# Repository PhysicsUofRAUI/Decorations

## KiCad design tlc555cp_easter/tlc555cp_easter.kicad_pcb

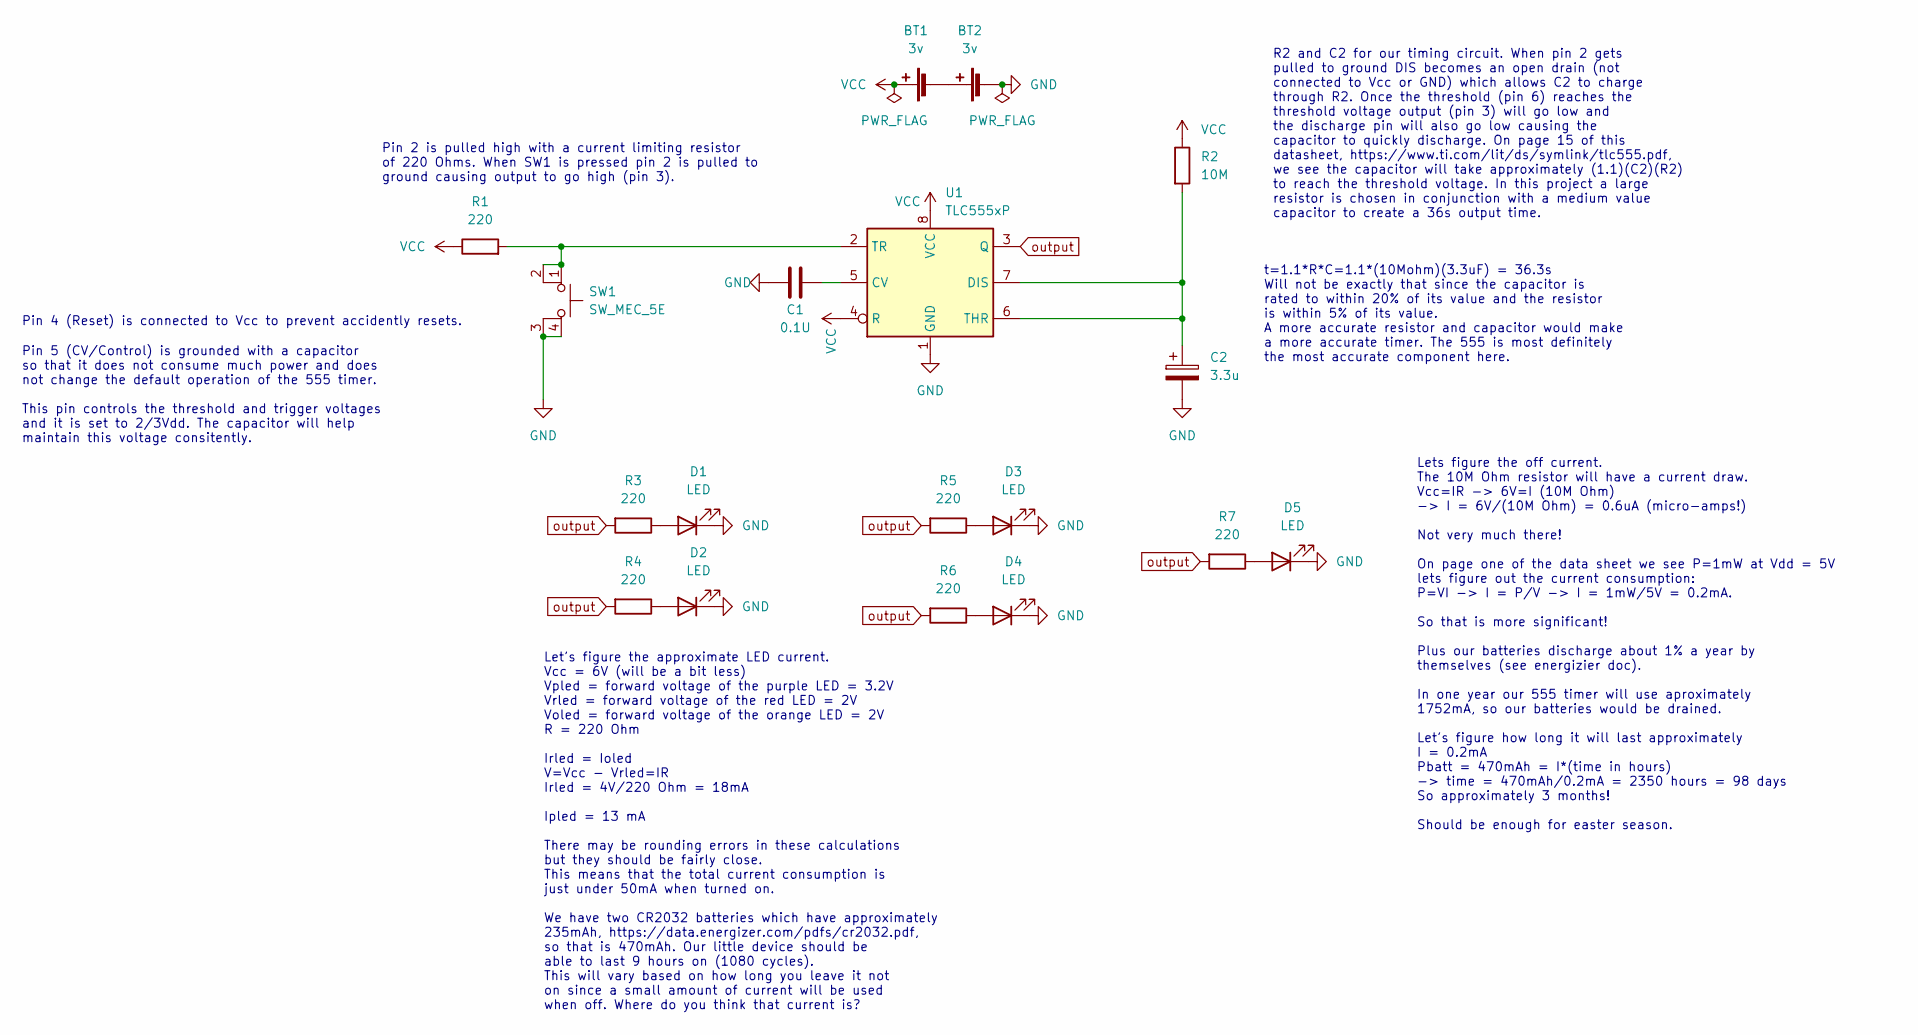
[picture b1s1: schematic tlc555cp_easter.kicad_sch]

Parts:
BT1, BT2: 3v; 1066
C1: 0.1U; CP_Radial_D5.0mm_P2.50mm
C2: 3.3u; CP_Radial_D5.0mm_P2.50mm
D1, D2, D3, D4, D5: LED; LED_D5.0mm
R1, R3, R4, R5, R6, R7: 220; R_Axial_DIN0204_L3.6mm_D1.6mm_P7.62mm_Horizontal
R2: 10M; R_Axial_DIN0204_L3.6mm_D1.6mm_P7.62mm_Horizontal
SW1: SW_MEC_5E; SW_PUSH-12mm_kody
U1: TLC555xP; DIP-8_W7.62mm

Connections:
GND: BT2.2 (-), C1.2, C2.2, D1.1 (K), D2.1 (K), D3.1 (K), D4.1 (K), D5.1 (K), SW1.3 (K), SW1.4 (A), U1.1 (GND)
unnamed: BT1.2 (-), BT2.1 (+)
unnamed: C2.1, R2.2, U1.6 (THR), U1.7 (DIS)
unnamed: D1.2 (A), R3.1
unnamed: D2.2 (A), R4.1
unnamed: D3.2 (A), R5.1
unnamed: D4.2 (A), R6.1
unnamed: D5.2 (A), R7.1
unnamed: R1.2, SW1.1, SW1.2, U1.2 (TR)
unnamed: C1.1, U1.5 (CV)
VCC: BT1.1 (+), R1.1, R2.1, U1.4 (R), U1.8 (VCC)
output: R3.2, R4.2, R5.2, R6.2, R7.2, U1.3 (Q)

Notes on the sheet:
Pin 4 (Reset) is connected to Vcc to prevent accidently resets.
t=1.1*R*C=1.1*(10Mohm)(3.3uF) = 36.3s Will not be exactly that since the capacitor is rated to within 20% of its value and the resistor is within 5% of its value. A more accurate resistor and capacitor would make a more accurate timer. The 555 is most definitely the most accurate component here.
Pin 2 is pulled high with a current limiting resistor of 220 Ohms. When SW1 is pressed pin 2 is pulled to ground causing output to go high (pin 3).
Pin 5 (CV/Control) is grounded with a capacitor so that it does not consume much power and does not change the default operation of the 555 timer. This pin controls the threshold and trigger voltages and it is set to 2/3Vdd. The capacitor will help maintain this voltage consitently.
Lets figure the off current. The 10M Ohm resistor will have a current draw. Vcc=IR -> 6V=I (10M Ohm) -> I = 6V/(10M Ohm) = 0.6uA (micro-amps!) Not very much there! On page one of the data sheet we see P=1mW at Vdd = 5V lets figure out the current consumption: P=VI -> I = P/V -> I = 1mW/5V = 0.2mA. 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
Let's figure the approximate LED current. Vcc = 6V (will be a bit less) Vpled = forward voltage of the purple LED = 3.2V Vrled = forward voltage of the red LED = 2V Voled = forward voltage of the orange LED = 2V R = 220 Ohm Irled = Ioled V=Vcc - Vrled=IR Irled = 4V/220 Ohm = 18mA Ipled = 13 mA Ther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
R2 and C2 for our timing circuit. When pin 2 gets pulled to ground DIS becomes an open drain (not connected to Vcc or GND) which allows C2 to charge through R2. Once the threshold (pin 6) reaches the threshold voltage output (pin 3) will go low and the discharge pin will also go low causing the cap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

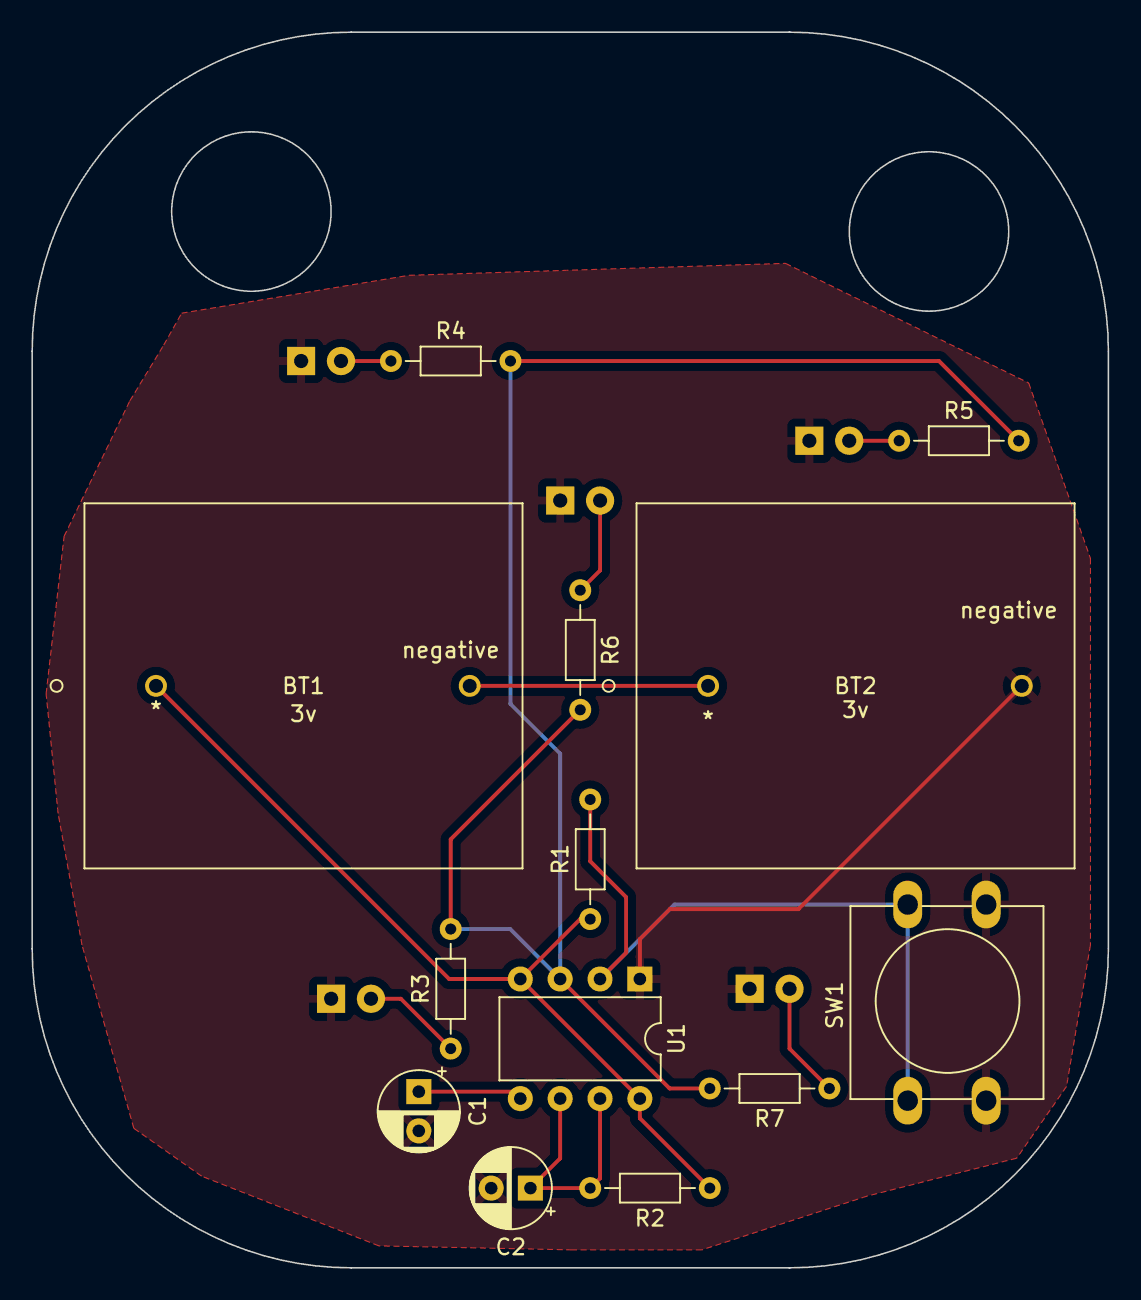
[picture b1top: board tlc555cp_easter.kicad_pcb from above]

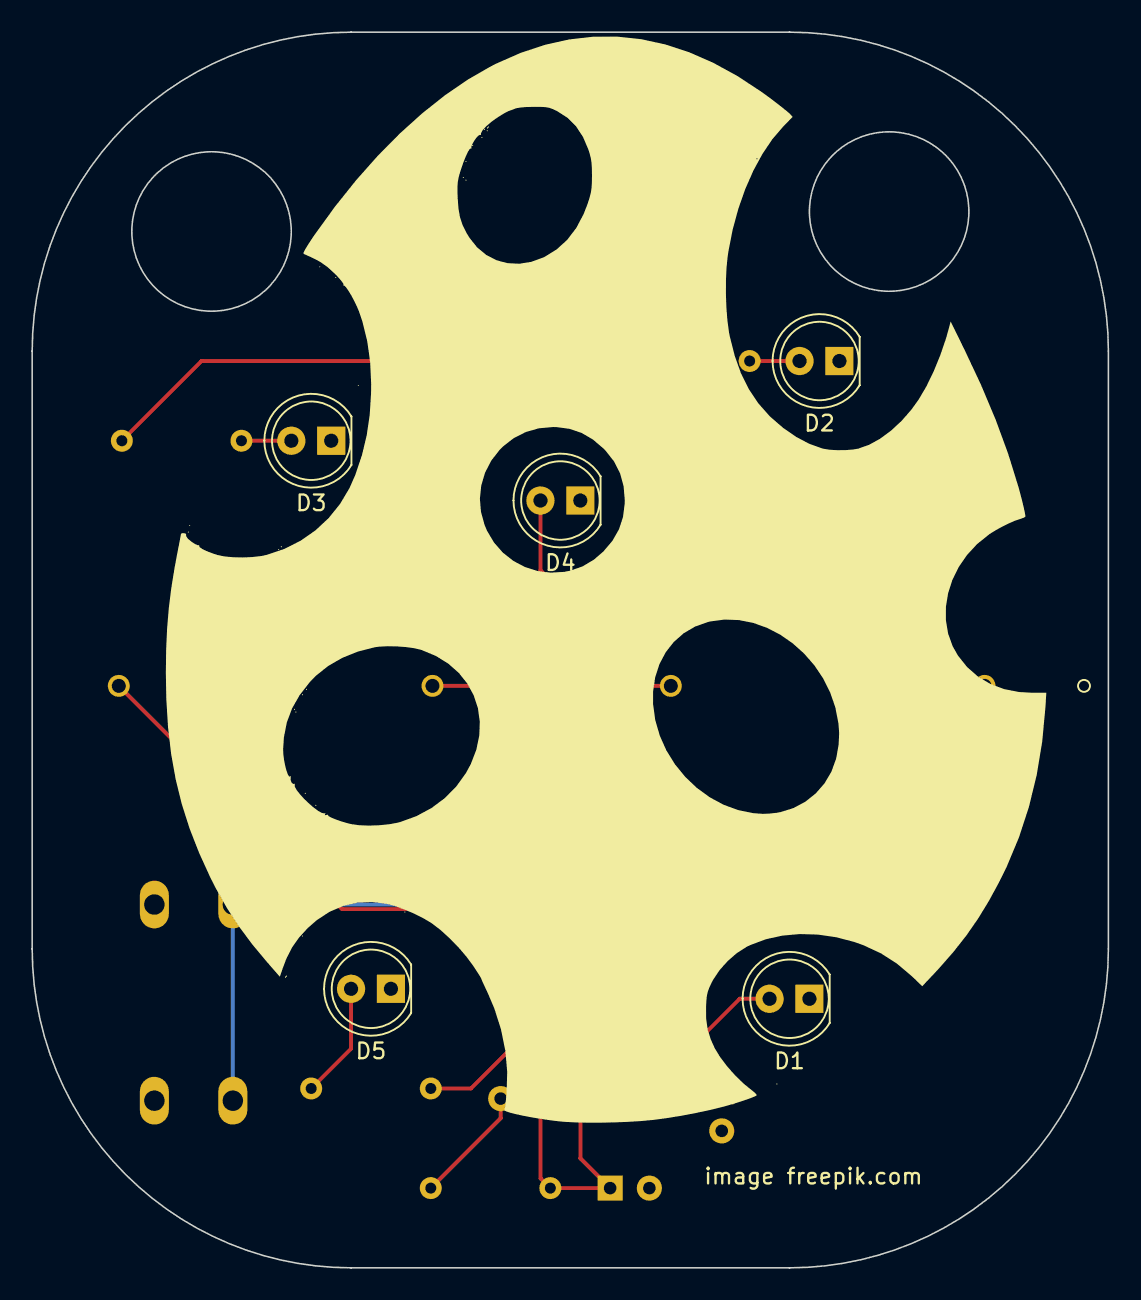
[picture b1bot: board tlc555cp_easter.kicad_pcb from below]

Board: 2 copper layers, 68.6 x 78.7 mm, 18 parts (5 on the bottom side), 12 nets.

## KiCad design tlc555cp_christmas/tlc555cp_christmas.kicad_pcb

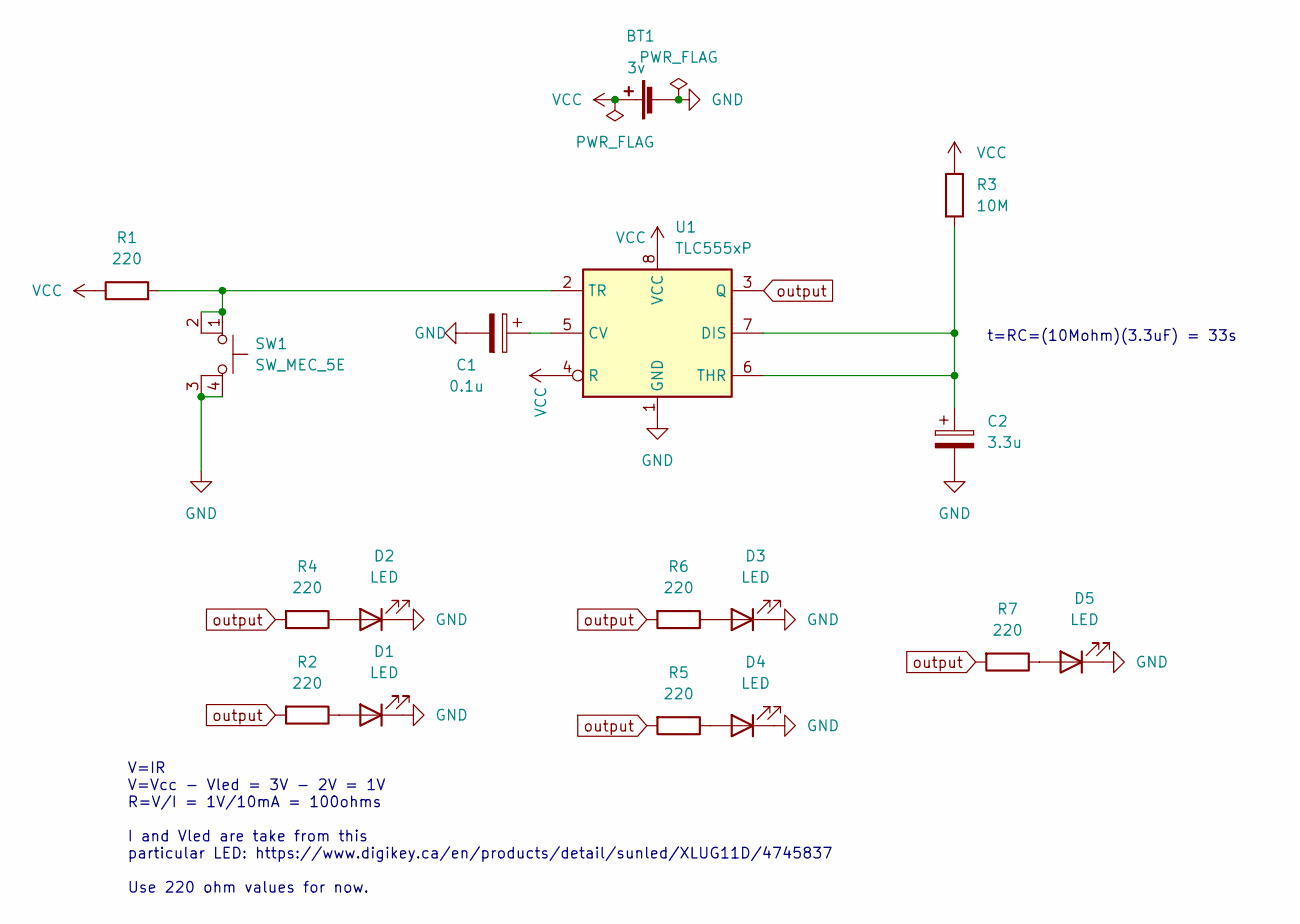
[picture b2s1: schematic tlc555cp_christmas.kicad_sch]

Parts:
BT1: 3v; 1066
C1: 0.1u; CP_Radial_D4.0mm_P2.00mm
C2: 3.3u; CP_Radial_D5.0mm_P2.50mm
D1, D2, D3, D4, D5: LED; LED_D5.0mm
R1, R2, R4, R5, R6, R7: 220; R_Axial_DIN0204_L3.6mm_D1.6mm_P5.08mm_Horizontal
R3: 10M; R_Axial_DIN0204_L3.6mm_D1.6mm_P5.08mm_Horizontal
SW1: SW_MEC_5E; SW_PUSH-12mm_kody
U1: TLC555xP; DIP-8_W7.62mm

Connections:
GND: BT1.2 (-), C1.2, C2.2, D1.1 (K), D2.1 (K), D3.1 (K), D4.1 (K), D5.1 (K), SW1.3 (K), SW1.4 (A), U1.1 (GND)
unnamed: C1.1, U1.5 (CV)
unnamed: C2.1, R3.2, U1.6 (THR), U1.7 (DIS)
unnamed: D1.2 (A), R2.1
unnamed: D2.2 (A), R4.1
unnamed: D3.2 (A), R6.1
unnamed: D4.2 (A), R5.1
unnamed: D5.2 (A), R7.1
unnamed: R1.2, SW1.1, SW1.2, U1.2 (TR)
VCC: BT1.1 (+), R1.1, R3.1, U1.4 (R), U1.8 (VCC)
output: R2.2, R4.2, R5.2, R6.2, R7.2, U1.3 (Q)

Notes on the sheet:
t=RC=(10Mohm)(3.3uF) = 33s
V=IR V=Vcc - Vled = 3V - 2V = 1V R=V/I = 1V/10mA = 100ohms I and Vled are take from this particular LED: https://www.digikey.ca/en/products/detail/sunled/XLUG11D/4745837 Use 220 ohm values for now.

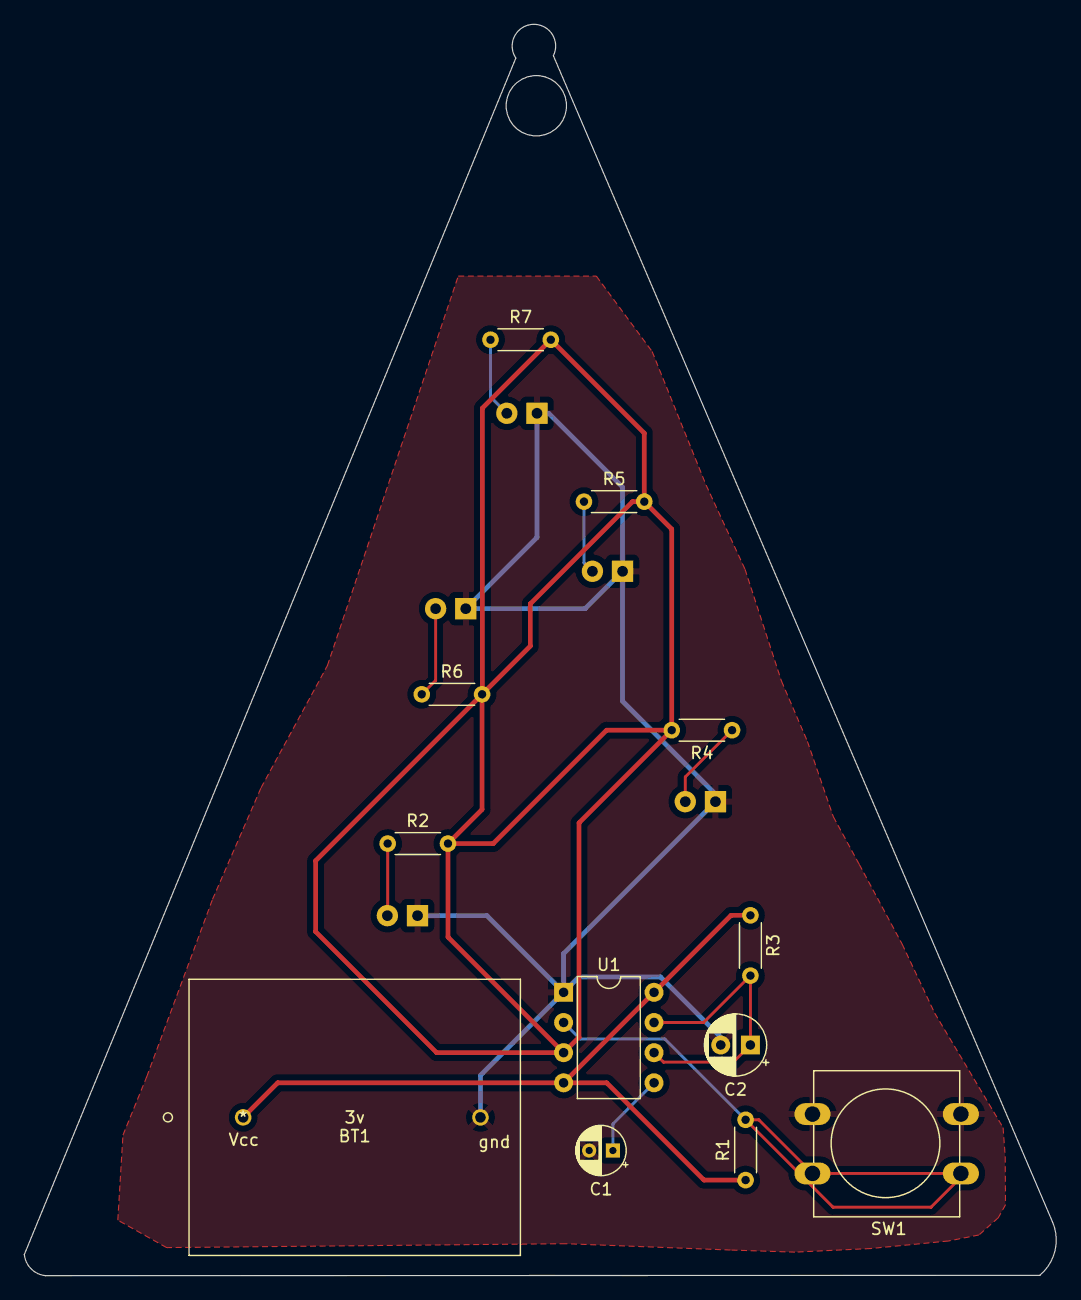
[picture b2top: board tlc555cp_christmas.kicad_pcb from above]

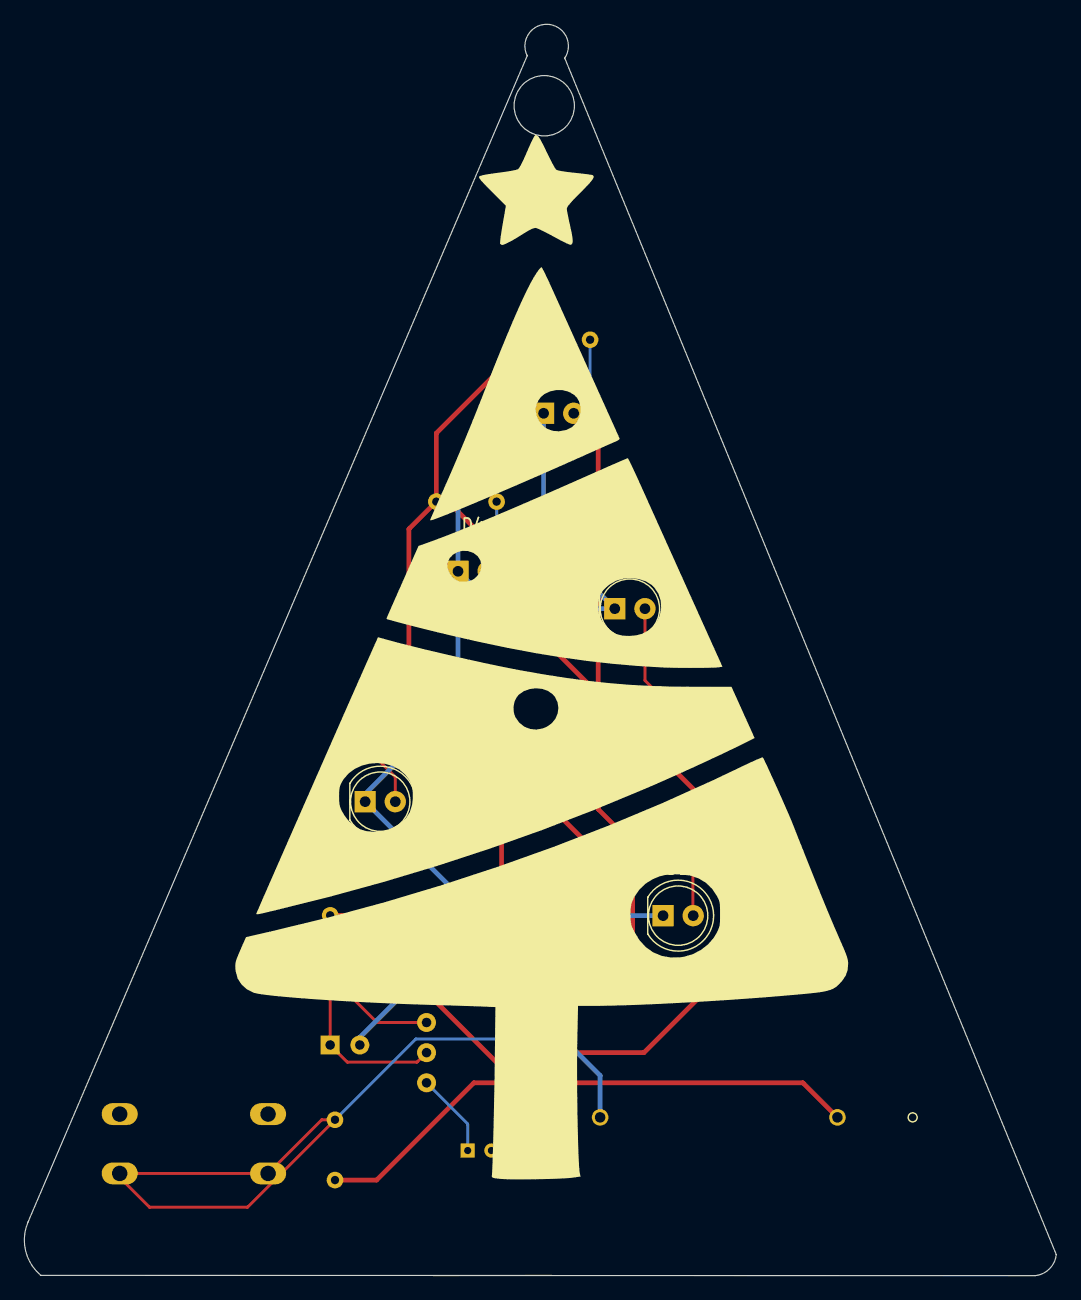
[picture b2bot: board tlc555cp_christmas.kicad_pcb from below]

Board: 2 copper layers, 86.9 x 105.4 mm, 17 parts (5 on the bottom side), 11 nets.

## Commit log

2023-01-07 intial commit for tree decoration
2023-01-07 update_gitignore
2023-01-08 update gitignore
2023-01-08 versior ordered on january 8 2023
2023-01-08 slight change on christmas pcb
2023-01-09 add easter decoration
2023-01-28 Fix switch footprint pad assignment.
2023-01-28 update gitiginor to ignore fp-info-cache
2023-01-28 fp-info not being tracked

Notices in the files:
parts and their libraries:
Copyright 2021 Accelerated Designs. All rights reserved.
